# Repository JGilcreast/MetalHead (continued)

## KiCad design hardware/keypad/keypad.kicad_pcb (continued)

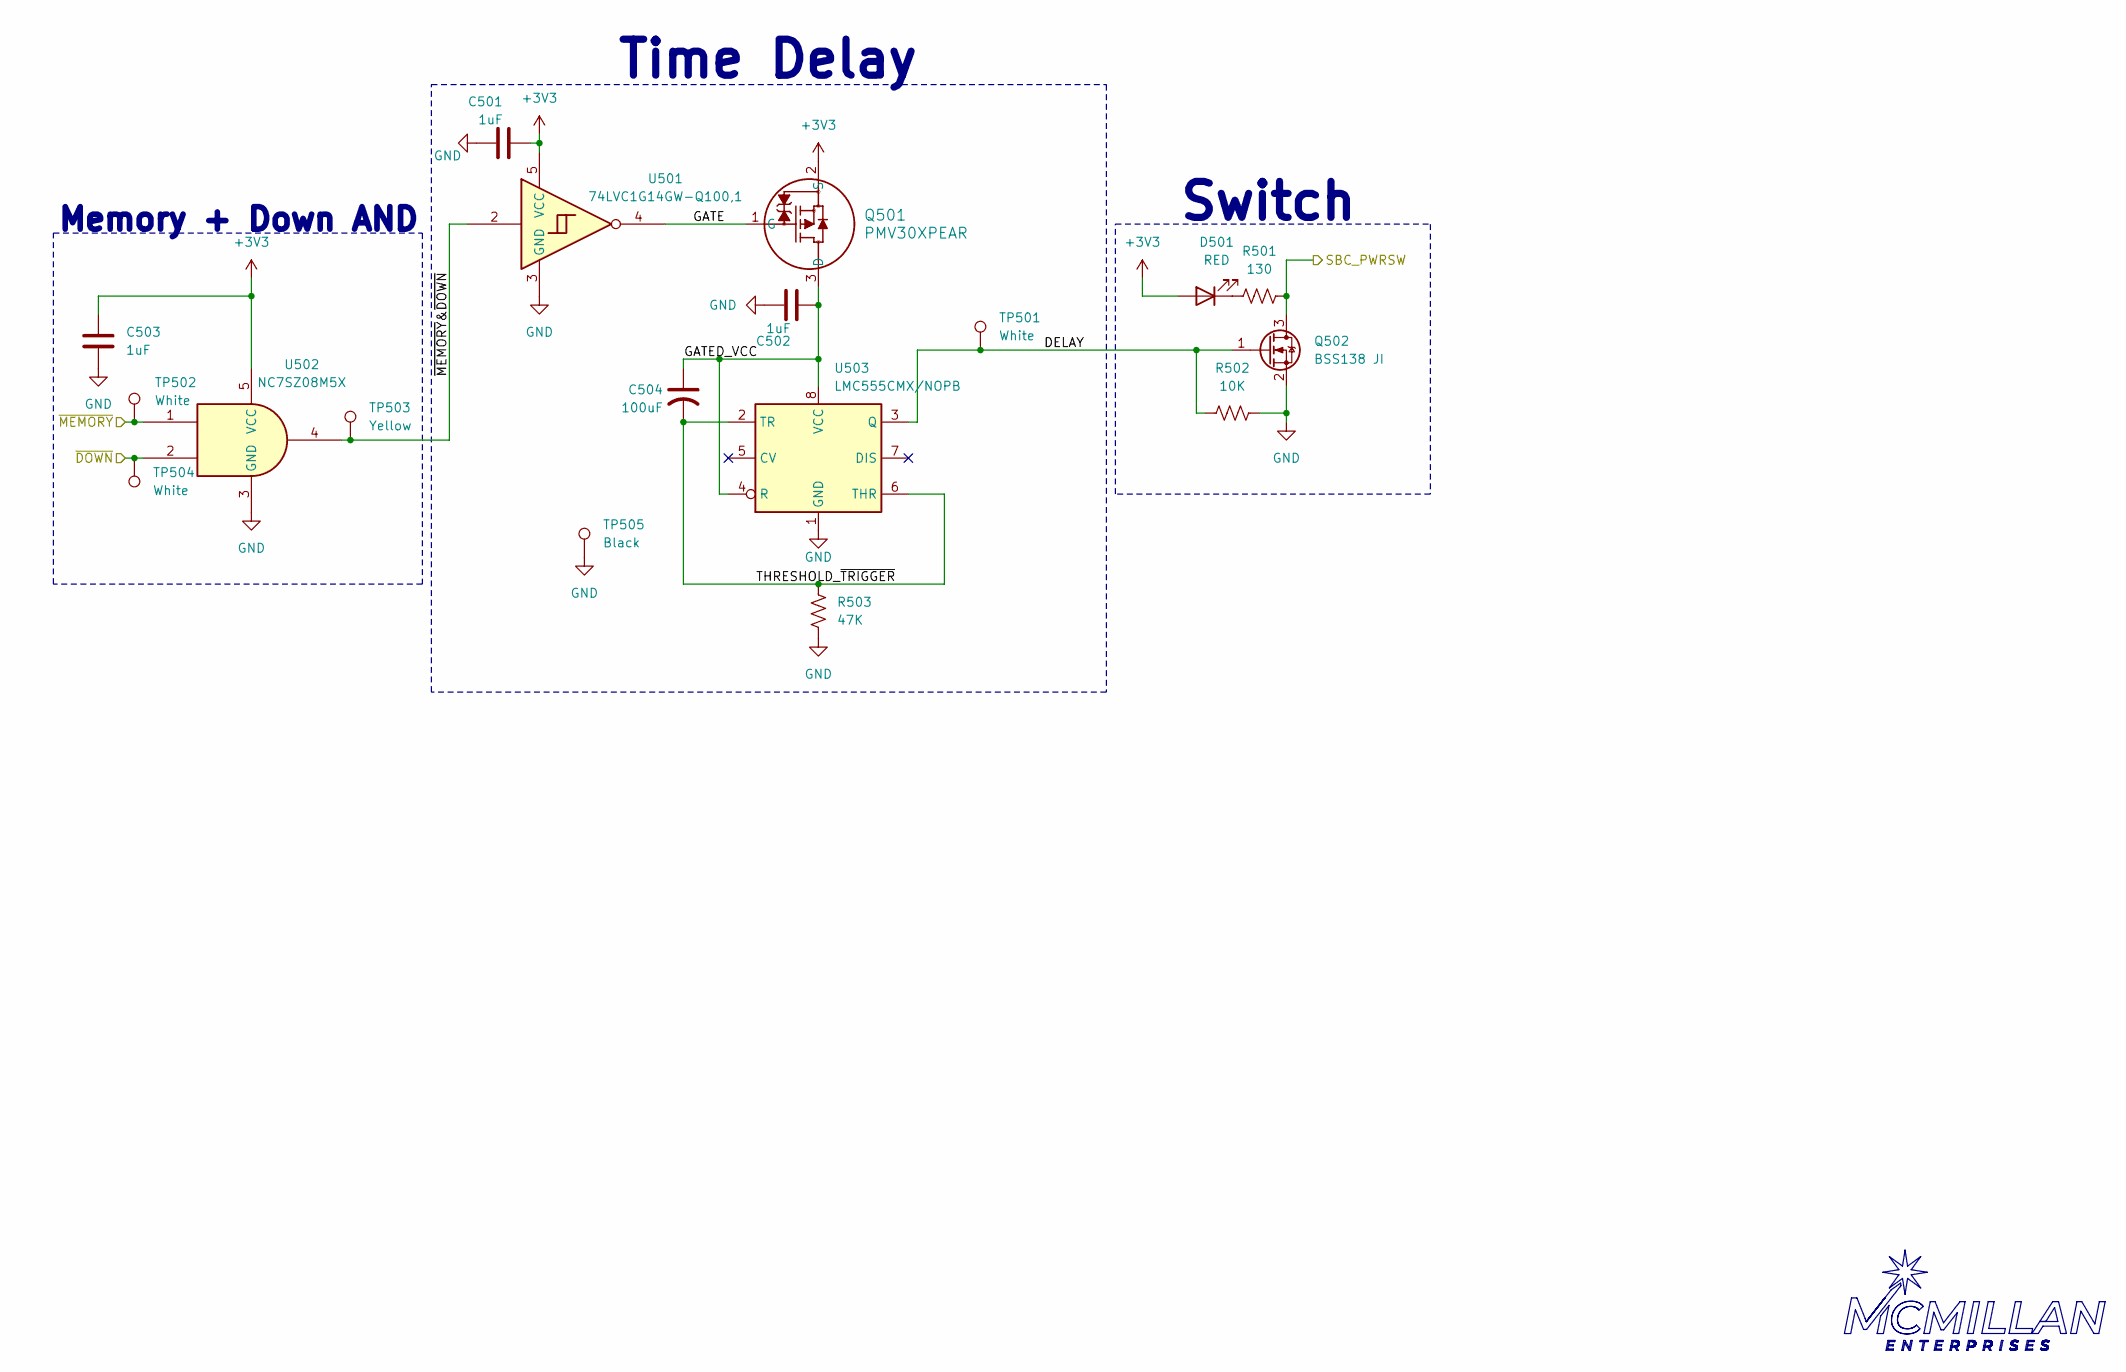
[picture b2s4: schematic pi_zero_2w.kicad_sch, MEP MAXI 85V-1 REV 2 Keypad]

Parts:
C501, C502, C503: 1uF; C_0805_2012Metric
C504: 100uF; C_Elec_6.3x5.4
D501: RED; LED_1206_3216Metric
Q501: PMV30XPEAR; SOT-23-3
Q502: BSS138 JI; SOT-23
R501: 130; R_0805_2012Metric
R502: 10K; R_0805_2012Metric
R503: 47K; R_0805_2012Metric
TP501, TP502, TP504: White; TestPoint_Keystone_5000-5004_Miniature
TP503: Yellow; TestPoint_Keystone_5000-5004_Miniature
TP505: Black; TestPoint_Keystone_5000-5004_Miniature
U501: 74LVC1G14GW-Q100,1; SOT-353_SC-70-5
U502: NC7SZ08M5X; SC-74A-5_1.55x2.9mm_P0.95mm
U503: LMC555CMX/NOPB; SOIC-8_3.9x4.9mm_P1.27mm

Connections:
+3V3: C501.1, C503.1, D501.2 (A), Q501.2 (S), U501.5 (VCC), U502.5 (VCC); also elsewhere on the board
/Debounce Switches/~DOWN: TP504.1, U502.2; also elsewhere on the board
/Debounce Switches/~MEMORY: TP502.1, U502.1; also elsewhere on the board
/PWRSW: Q502.3 (D), R501.1; also elsewhere on the board
/Pi Zero 2W Power Reset/DELAY: Q502.1 (G), R502.2, TP501.1, U503.3 (Q)
/Pi Zero 2W Power Reset/GATE: Q501.1 (G), U501.4
/Pi Zero 2W Power Reset/GATED_VCC: C502.1, C504.1, Q501.3 (D), U503.4 (R), U503.8 (VCC)
/Pi Zero 2W Power Reset/THRESHOLD_~TRIGGER: C504.2, R503.1, U503.2 (TR), U503.6 (THR)
/Pi Zero 2W Power Reset/~MEMORY&~DOWN: TP503.1, U501.2, U502.4
GND: C501.2, C502.2, C503.2, Q502.2 (S), R502.1, R503.2, TP505.1, U501.3 (GND), U502.3 (GND), U503.1 (GND); also elsewhere on the board
unnamed: D501.1 (K), R501.2

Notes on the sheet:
Switch
Time Delay
Memory + Down AND

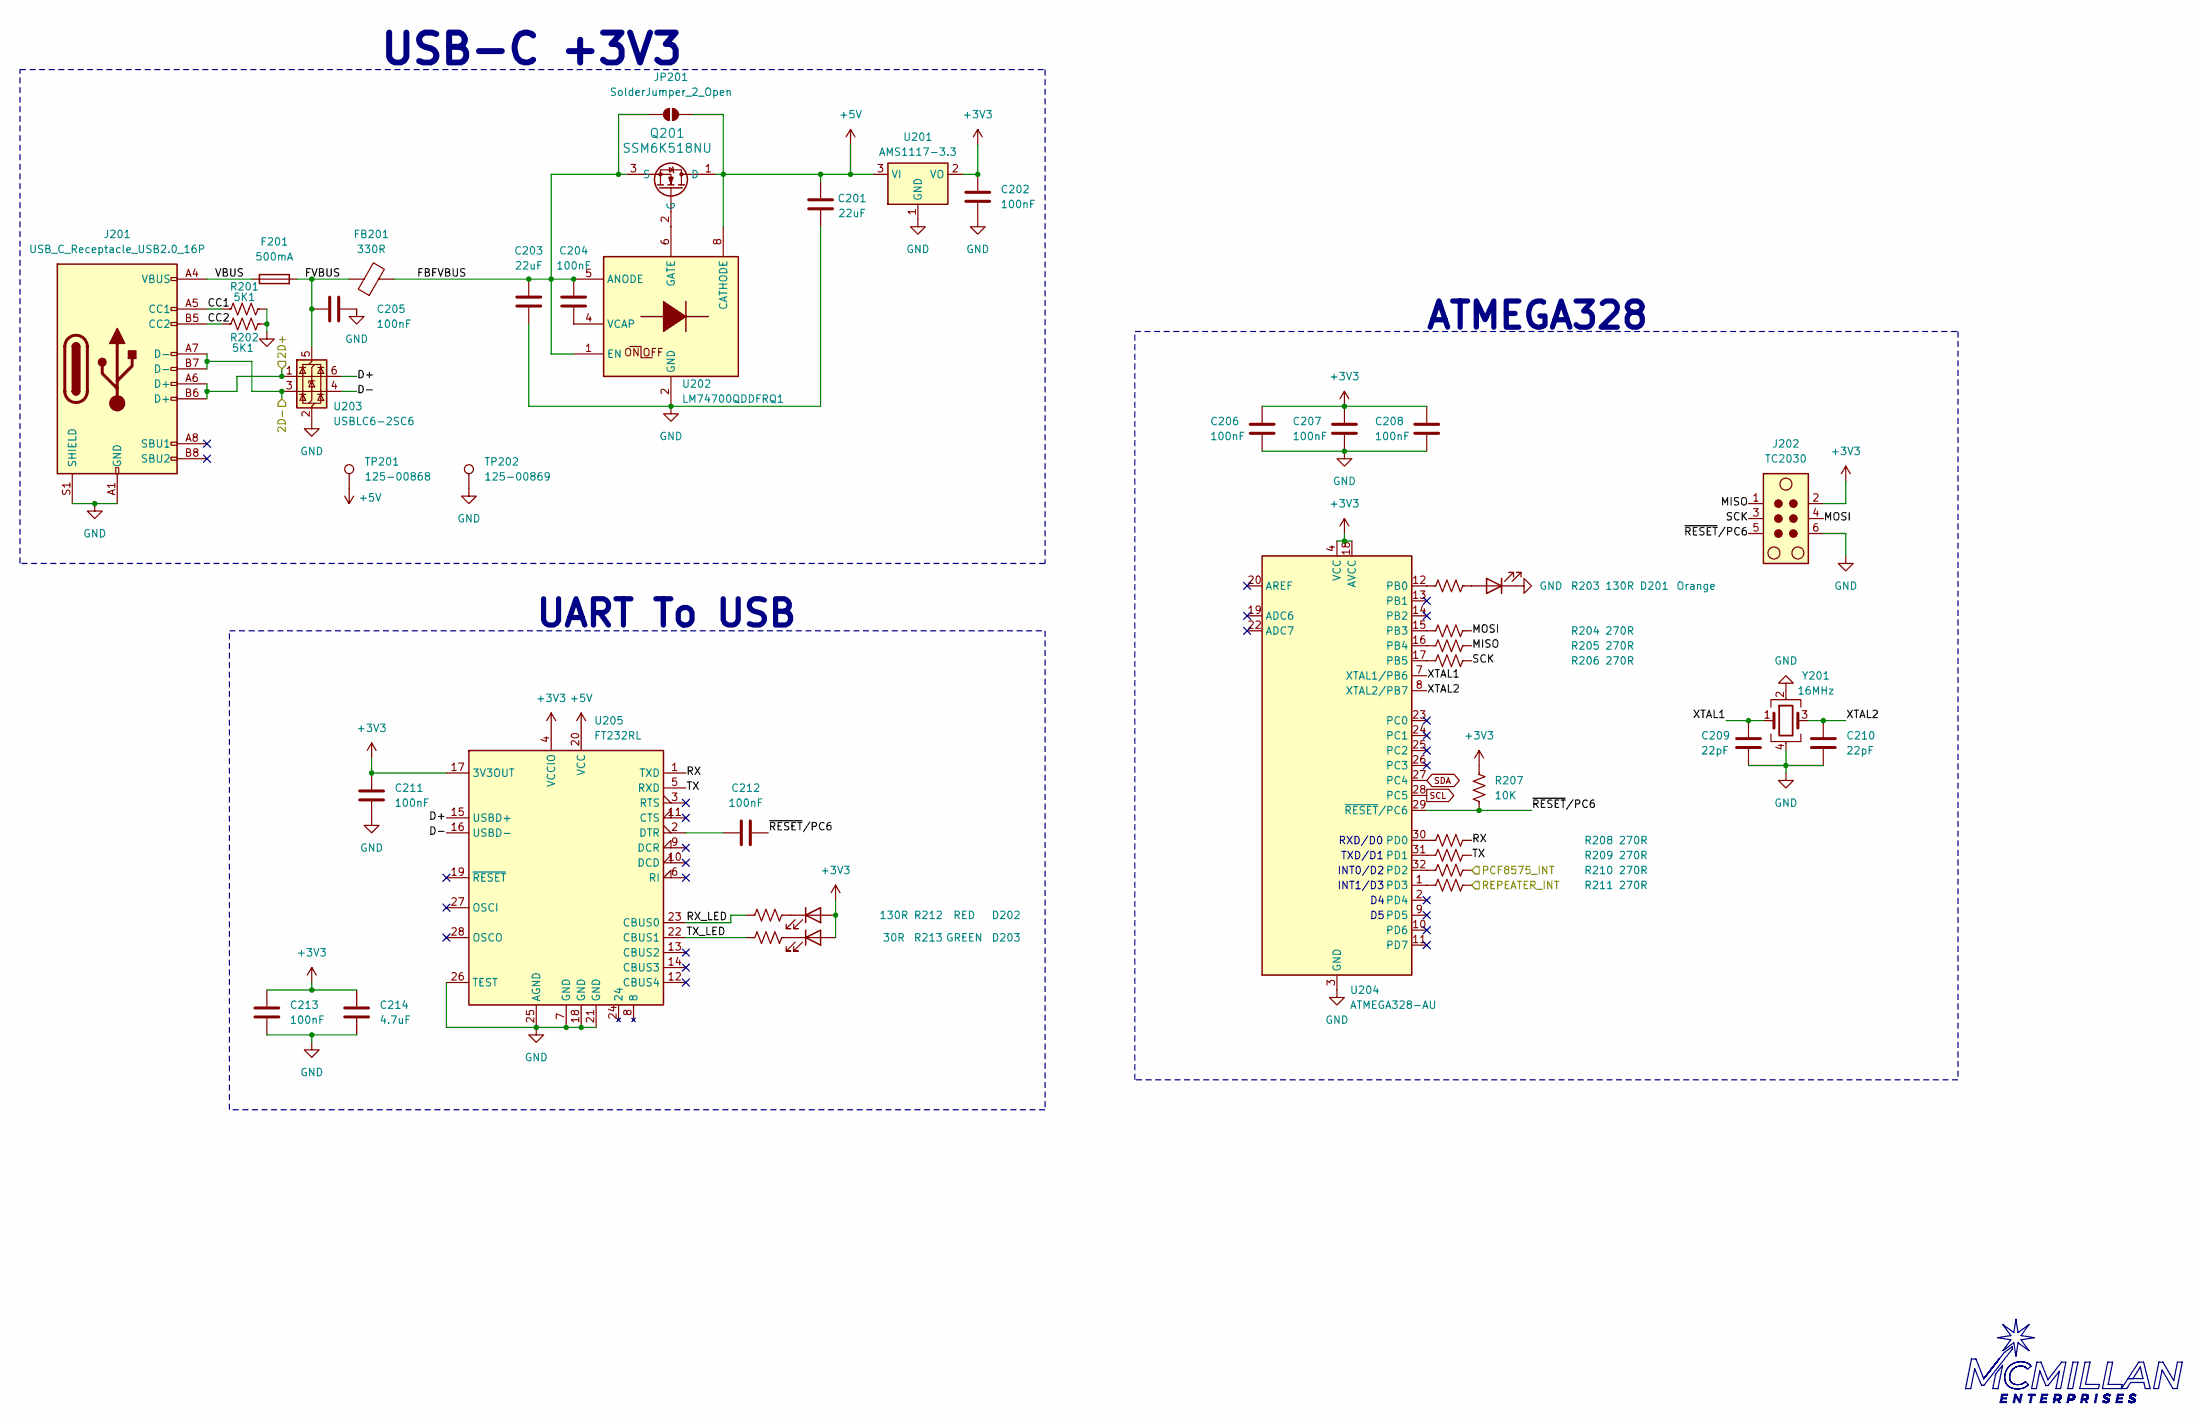
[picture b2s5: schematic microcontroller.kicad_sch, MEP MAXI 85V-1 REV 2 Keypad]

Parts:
C201, C203: 22uF; C_1206_3216Metric
C202, C205, C206, C207, C208, C211, C212, C213: 100nF; C_0805_2012Metric
C204: 100nF; C_1206_3216Metric
C209, C210: 22pF; C_0805_2012Metric
C214: 4.7uF; C_0805_2012Metric
D201: Orange; LED_0805_2012Metric
D202: RED; LED_0805_2012Metric
D203: GREEN; LED_0805_2012Metric
F201: 500mA; Fuse_0805_2012Metric
FB201: 330R; L_0805_2012Metric
J201: USB_C_Receptacle_USB2.0_16P; USB_C_Receptacle_G-Switch_GT-USB-7010ASV
J202: TC2030; Tag-Connect_TC2030-IDC-NL_2x03_P1.27mm_Vertical
JP201: SolderJumper_2_Open; SolderJumper-2_P1.3mm_Open_TrianglePad1.0x1.5mm
Q201: SSM6K518NU; SOT-1220UDFN6B_TOS
R201, R202: 5K1; R_0805_2012Metric
R203, R212: 130R; R_0805_2012Metric
R204, R205, R206, R208, R209, R210, R211: 270R; R_0805_2012Metric
R207: 10K; R_0805_2012Metric
R213: 30R; R_0805_2012Metric
TP201: 125-00868; TestPoint_Keystone_5000-5004_Miniature
TP202: 125-00869; TestPoint_Keystone_5000-5004_Miniature
U201: AMS1117-3.3; SOT-223-3_TabPin2
U202: LM74700QDDFRQ1; SOT65P280X110-8N; Mouser Part Number 595-LM74700QDDFRQ1
U203: USBLC6-2SC6; SOT-23-6
U204: ATMEGA328-AU; TQFP-32_7x7mm_P0.8mm
U205: FT232RL; SSOP-28_5.3x10.2mm_P0.65mm
Y201: 16MHz; Crystal_SMD_3225-4Pin_3.2x2.5mm

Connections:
+3V3: C202.1, C206.1, C207.1, C208.1, C211.1, C213.1, C214.1, D202.2 (A), D203.2 (A), J202.2, R207.1, U201.2 (VO), U204.4 (VCC), U204.6 (VCC), U204.18 (AVCC), U205.4 (VCCIO), U205.17 (3V3OUT); also elsewhere on the board
/Microcontroller/CC1: J201.A5 (CC1), R201.2
/Microcontroller/CC2: J201.B5 (CC2), R202.2
/Microcontroller/D+: U203.6 (I/O1), U205.15 (USBD+)
/Microcontroller/D-: U203.4 (I/O2), U205.16 (USBD-)
/Microcontroller/FBFVBUS: C203.1, C204.1, FB201.2, JP201.1 (A), Q201.3 (S), U202.1 (EN), U202.5 (ANODE)
/Microcontroller/FVBUS: C205.2, F201.2, FB201.1, U203.5 (VBUS)
/Microcontroller/MISO: J202.1, R205.2
/Microcontroller/MOSI: J202.4, R204.2
/Microcontroller/RX: R208.2, U205.1 (TXD)
/Microcontroller/RX_LED: R212.2, U205.23 (CBUS0)
/Microcontroller/SCK: J202.3, R206.2
/Microcontroller/TX: R209.2, U205.5 (RXD)
/Microcontroller/TX_LED: R213.2, U205.22 (CBUS1)
/Microcontroller/VBUS: F201.1, J201.A4 (VBUS), J201.A9 (VBUS), J201.B4 (VBUS), J201.B9 (VBUS)
/Microcontroller/XTAL1: C209.1, U204.7 (XTAL1/PB6), Y201.1
/Microcontroller/XTAL2: C210.1, U204.8 (XTAL2/PB7), Y201.3
/Microcontroller/~RESET/PC6: C212.2, J202.5, R207.2, U204.29 (~RESET/PC6)
/PCF8575_INT: R210.2; also elsewhere on the board
/REPEATER_INT: R211.2; also elsewhere on the board
/USB3-D+: J201.A6 (D+), J201.B6 (D+), U203.1 (I/O1); also elsewhere on the board
/USB3-D-: J201.A7 (D-), J201.B7 (D-), U203.3 (I/O2); also elsewhere on the board
GND: C201.2, C202.2, C203.2, C205.1, C206.2, C207.2, C208.2, C209.2, C210.2, C211.2, C213.2, C214.2, D201.1 (K), J201.A1 (GND), J201.A12 (GND), J201.B1 (GND), J201.B12 (GND), J201.S1 (SHIELD), J202.6, R201.1, R202.1, TP202.1, U201.1 (GND), U202.2 (GND), U203.2 (GND), U204.3 (GND), U204.5 (GND), U204.21 (GND), U205.7 (GND), U205.18 (GND), U205.21 (GND), U205.25 (AGND), U205.26 (TEST), Y201.2, Y201.4; also elsewhere on the board
unnamed: D201.2 (A), R203.2
unnamed: D202.1 (K), R212.1
unnamed: D203.1 (K), R213.1
unnamed: C204.2, U202.4 (VCAP)
unnamed: R203.1, U204.12 (PB0)
unnamed: R204.1, U204.15 (PB3)
unnamed: R205.1, U204.16 (PB4)
unnamed: R206.1, U204.17 (PB5)
unnamed: R208.1, U204.30 (PD0)
unnamed: R209.1, U204.31 (PD1)
unnamed: R210.1, U204.32 (PD2)
unnamed: R211.1, U204.1 (PD3)
unnamed: C212.1, U205.2 (DTR)
SCL: U204.28 (PC5); also elsewhere on the board
SDA: U204.27 (PC4); also elsewhere on the board

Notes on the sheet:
RXD/D0
INT1/D3
ATMEGA328
INT0/D2
USB-C +3V3
UART To USB
TXD/D1

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
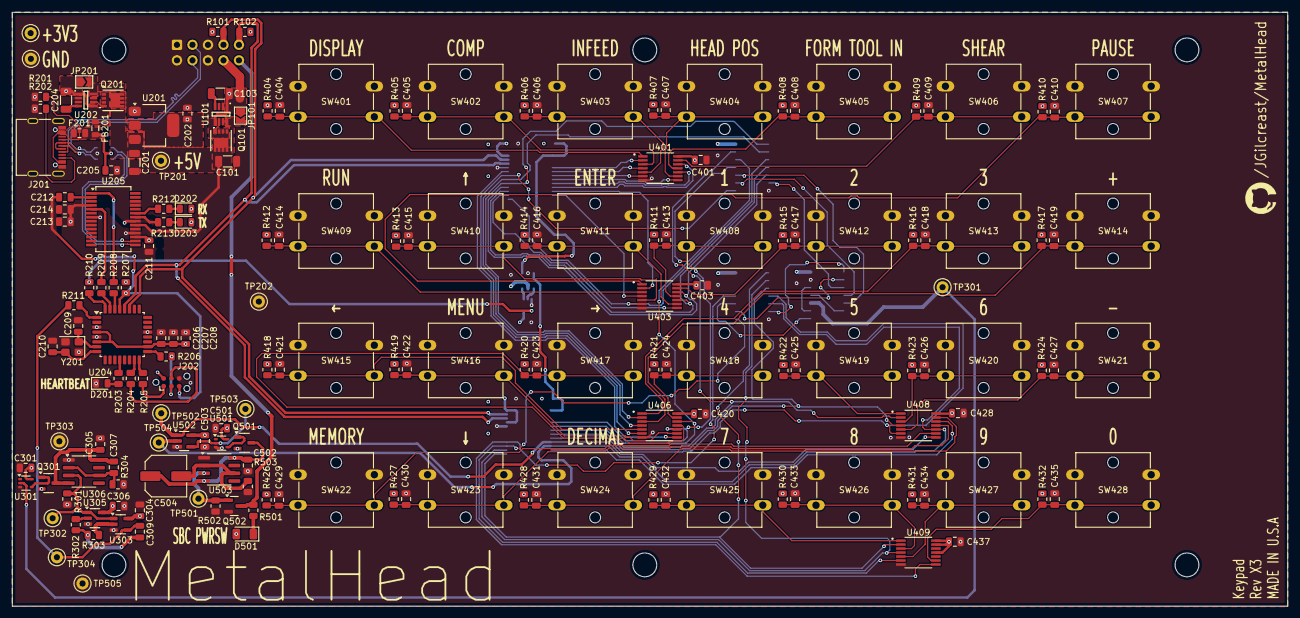
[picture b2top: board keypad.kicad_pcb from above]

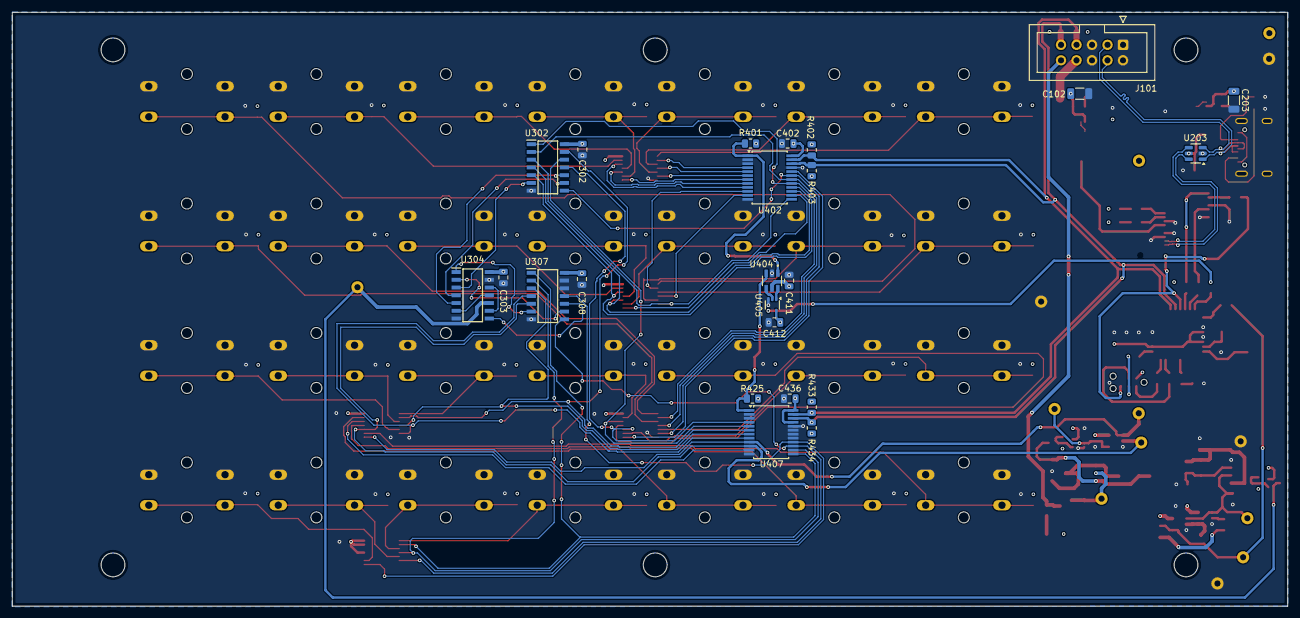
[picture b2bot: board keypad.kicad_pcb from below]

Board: 4 copper layers, 209.0 x 97.3 mm, 206 parts (24 on the bottom side), 126 nets.
